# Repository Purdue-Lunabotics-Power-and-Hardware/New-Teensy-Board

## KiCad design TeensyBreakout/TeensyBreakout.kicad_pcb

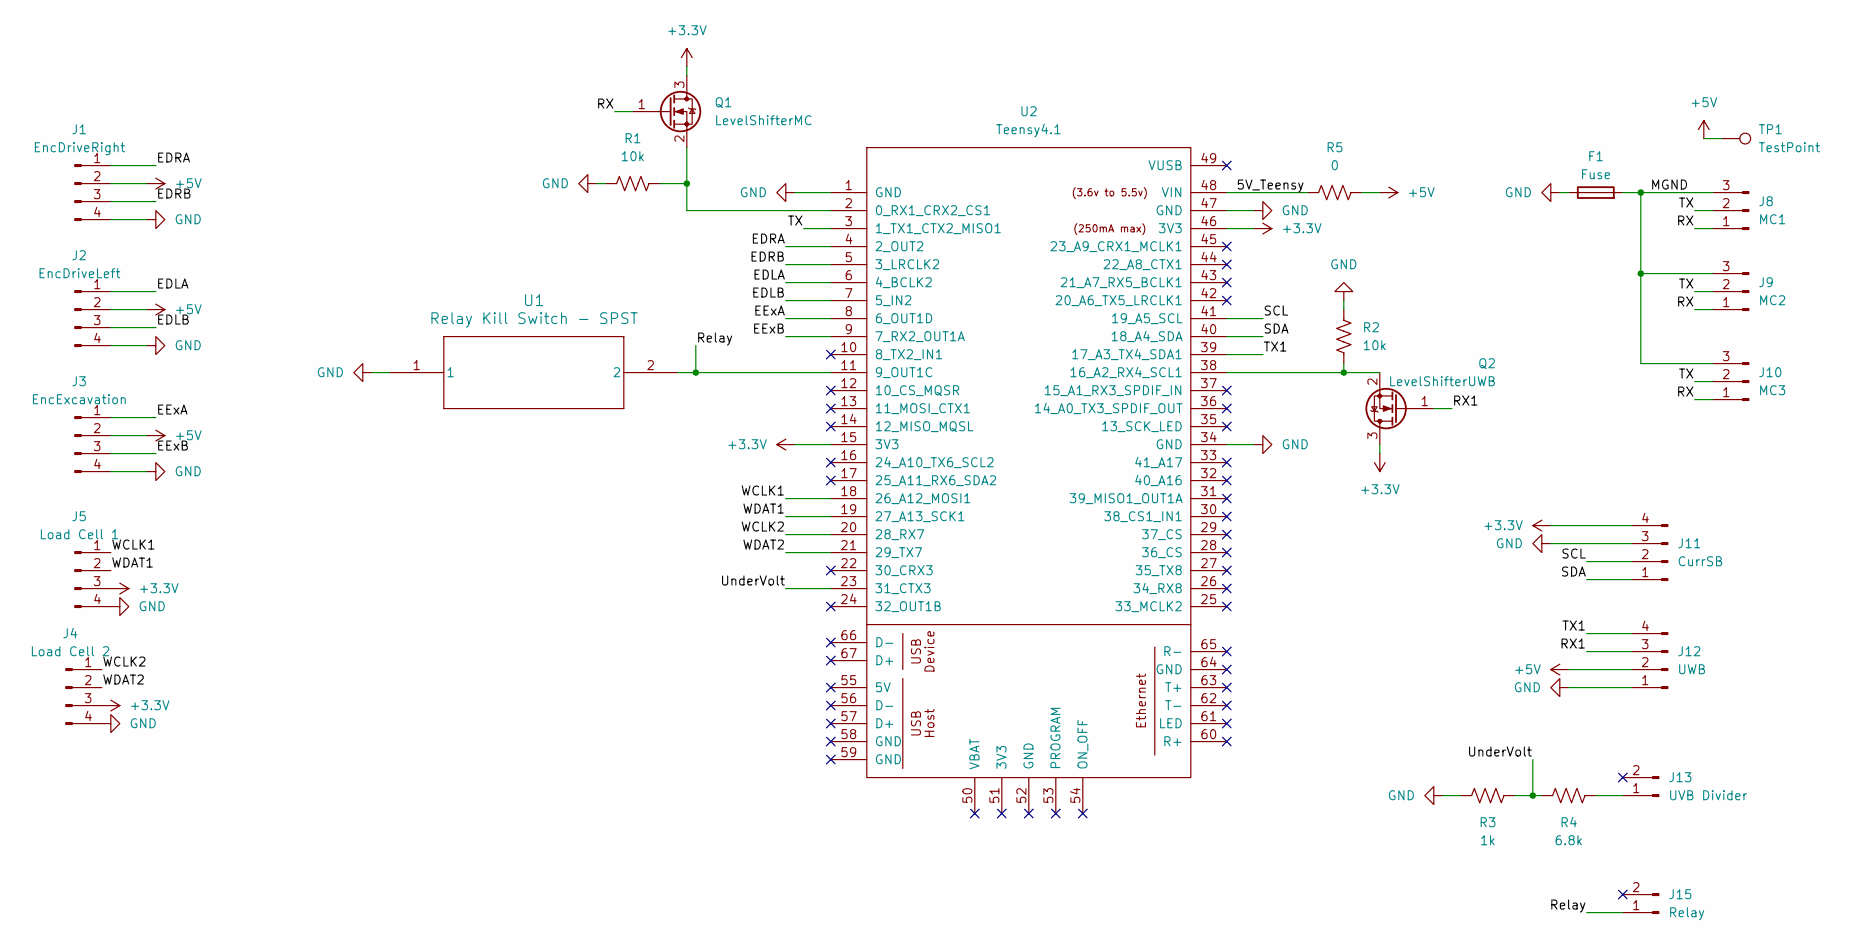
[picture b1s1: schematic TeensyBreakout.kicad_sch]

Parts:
F1: Fuse; R_0603_1608Metric_Pad0.98x0.95mm_HandSolder
J1: EncDriveRight; 4pinJST
J2: EncDriveLeft; 4pinJST
J3: EncExcavation; 4pinJST
J4: Load Cell 2; 4pinJST
J5: Load Cell 1; 4pinJST
J8: MC1; 3pinJST
J9: MC2; 3pinJST
J10: MC3; 3pinJST
J11: CurrSB; 4pinJST
J12: UWB; 4pinJST
J13: UVB Divider; 2pinJST
J15: Relay; 2pinJST
Q1: LevelShifterMC; SOT-23
Q2: LevelShifterUWB; SOT-23
R1, R2: 10k; 10kOhmRes
R3: 1k; 10kOhmRes
R4: 6.8k; 10kOhmRes
R5: 0; R_0805_2012Metric_Pad1.20x1.40mm_HandSolder
TP1: TestPoint; Pin_D0.9mm_L10.0mm_W2.4mm_FlatFork
U1: Relay Kill Switch - SPST; RR511D1121_EWI
U2: Teensy4.1; Teensy41

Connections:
+3.3V: J4.3, J5.3, J11.4, Q1.3 (D), Q2.3 (D), U2.15 (3V3), U2.46 (3V3)
+5V: J1.2, J2.2, J3.2, J12.2, R5.1, TP1.1; also elsewhere on the board
/5V_Teensy: R5.2, U2.48 (VIN)
/EDLA: J2.1, U2.6 (4_BCLK2)
/EDLB: J2.3, U2.7 (5_IN2)
/EDRA: J1.1, U2.4 (2_OUT2)
/EDRB: J1.3, U2.5 (3_LRCLK2)
/EExA: J3.1, U2.8 (6_OUT1D)
/EExB: J3.3, U2.9 (7_RX2_OUT1A)
/MGND: F1.2, J8.3, J9.3, J10.3
/RX: J8.1, J9.1, J10.1, Q1.1 (G)
/RX1: J12.3, Q2.1 (G)
/Relay: J15.1, U1.2, U2.11 (9_OUT1C)
/SCL: J11.2, U2.41 (19_A5_SCL)
/SDA: J11.1, U2.40 (18_A4_SDA)
/TX: J8.2, J9.2, J10.2, U2.3 (1_TX1_CTX2_MISO1)
/TX1: J12.4, U2.39 (17_A3_TX4_SDA1)
/UnderVolt: R3.1, R4.2, U2.23 (31_CTX3)
/WCLK1: J5.1, U2.18 (26_A12_MOSI1)
/WCLK2: J4.1, U2.20 (28_RX7)
/WDAT1: J5.2, U2.19 (27_A13_SCK1)
/WDAT2: J4.2, U2.21 (29_TX7)
GND: F1.1, J1.4, J2.4, J3.4, J4.4, J5.4, J11.3, J12.1, R1.1, R2.2, R3.2, U1.1, U2.1 (GND), U2.34 (GND), U2.47 (GND)
unnamed: J13.1, R4.1
unnamed: Q1.2 (S), R1.2, U2.2 (0_RX1_CRX2_CS1)
unnamed: Q2.2 (S), R2.1, U2.38 (16_A2_RX4_SCL1)

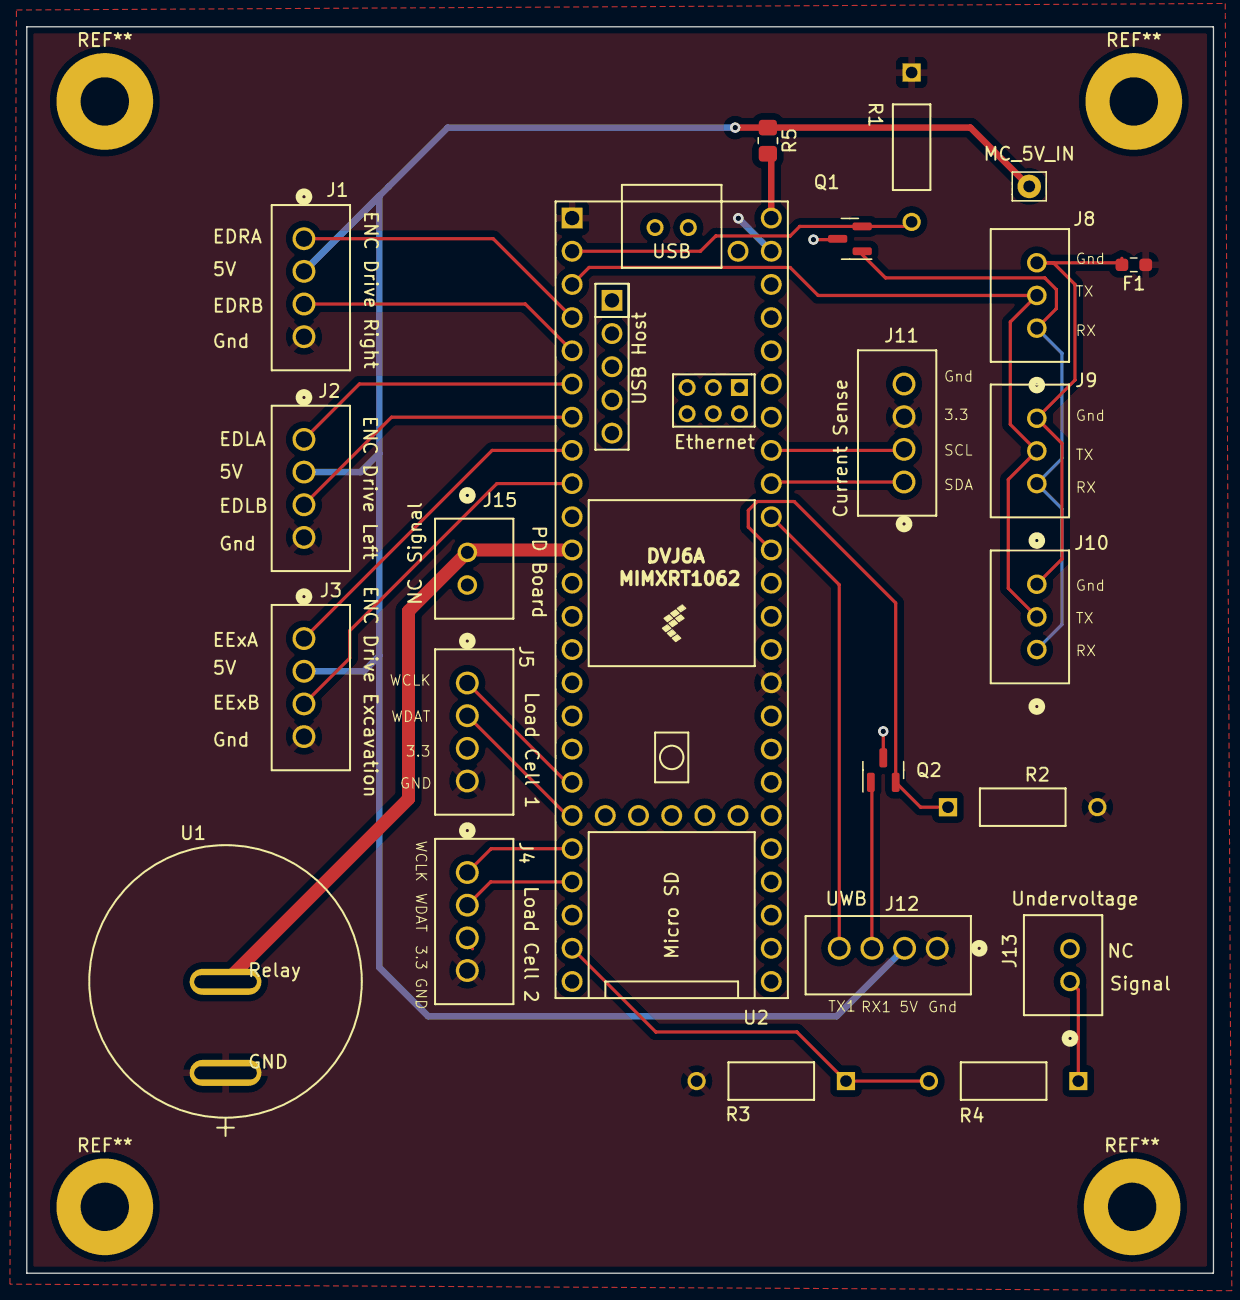
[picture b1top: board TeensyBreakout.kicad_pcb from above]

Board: 2 copper layers, 90.8 x 95.4 mm, 23 parts (0 on the bottom side), 26 nets.

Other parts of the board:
MC_5V_IN: TestPoint; Pin_D0.9mm_L10.0mm_W2.4mm_FlatFork

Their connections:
+5V: MC_5V_IN.1; also elsewhere on the board

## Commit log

2024-03-27 minor changes
2024-03-28 added silkscreen
2024-03-28 added mounting
2024-03-28 added fuses to gnd input from MCs
